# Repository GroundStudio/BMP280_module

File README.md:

GroundStudio BMP280 module
====================================

Get it from [ardushop.ro](https://ardushop.ro/ro/118-groundstudio)

Explore all the GroundStudio products at [GroundStudio.ro](https://groundstudio.ro/)

Description
-------------------
The module integrates the BMP280 temperature and atmospheric pressure sensor that uses the I²C and SPI standards for communication so it can be easily used together with most existing development boards.

Contents
-------------------

* [/Hardware](https://github.com/GroundStudio/BMP280_module/tree/main/Hardware) -- Schematics, layout.

Versions
-------------------
*(Not all tags shown)*

- [REV 1.0.0]

License
-------------------

This is released under the [Attribution-ShareAlike 4.0 International (CC BY-SA 4.0)](https://creativecommons.org/licenses/by-sa/4.0/) license.
**You are welcome to use this for commercial purposes.**

Please consider contributing back to this project or others to help the open-source hardware community continue to thrive and grow!

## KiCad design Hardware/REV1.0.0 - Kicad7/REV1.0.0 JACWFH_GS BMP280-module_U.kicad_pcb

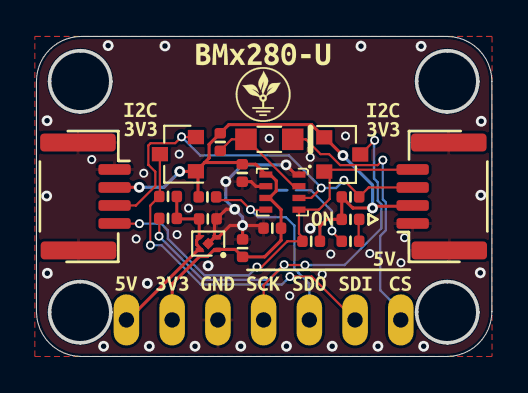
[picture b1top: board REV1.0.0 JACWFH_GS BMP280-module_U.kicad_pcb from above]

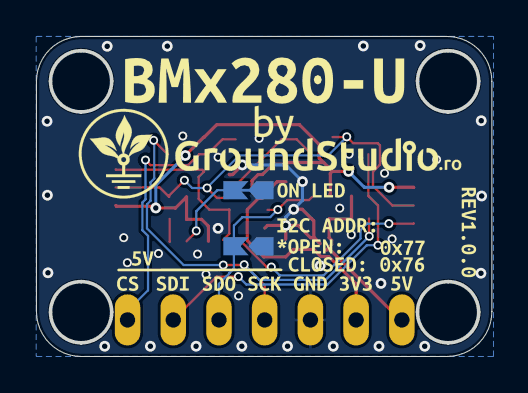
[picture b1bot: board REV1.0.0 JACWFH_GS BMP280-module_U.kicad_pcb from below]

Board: 2 copper layers, 25.2 x 17.6 mm, 51 parts (18 on the bottom side), 12 nets.

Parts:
C1, C2: C_0402_100nF_16V; C_0402_alt
C3, C4: C_0402_1uF_10V; C_0402_alt
D2: 1N4148WS; SOD-323
J1: Conn_01x07; PinHeader_1x07_P2.54mm_Vertical_Male
J2: LED disable; SolderJumper_NC
J4: SolderJumper_NO
LED1: ON_LED; LED_0402_alt
Q1, Q2: BSS138; SOT-23
R1, R2, R3, R4, R5, R6, R7: R_0402_10k; R_0402_alt
REG1: FBP1-1-4_ME6211C33U4AG-N; FBP1-1-4
U1: BMP280; LGA-8_2x2.5mm_BMP&BME280
X1, X2: SH_1x04_P1.0_H; SH__1x04_P1.00mm_Horizontal
kibuzzard-6343EE4B: G***; kibuzzard-6343EE4B
kibuzzard-6343F6DB: G***; kibuzzard-6343F6DB
kibuzzard-6343F70F: G***; kibuzzard-6343F70F
kibuzzard-6343F74A, kibuzzard-6343F74A#2: G***; kibuzzard-6343F74A
kibuzzard-6343F740, kibuzzard-6343F740#2: G***; kibuzzard-6343F740
kibuzzard-6343FCC8, kibuzzard-6343FCC8#2: G***; kibuzzard-6343FCC8
kibuzzard-6343FCE2: G***; kibuzzard-6343FCE2
kibuzzard-6343FCED, kibuzzard-6343FCED#2, kibuzzard-6343FCED#3, kibuzzard-6343FCED#4: G***; kibuzzard-6343FCED
kibuzzard-6343FD2F, kibuzzard-6343FD2F#2: G***; kibuzzard-6343FD2F
kibuzzard-6343FD19, kibuzzard-6343FD19#2: G***; kibuzzard-6343FD19
kibuzzard-6343FD42, kibuzzard-6343FD42#2: G***; kibuzzard-6343FD42
kibuzzard-6343FED9, kibuzzard-6343FED9#2: G***; kibuzzard-6343FED9
kibuzzard-6343FEE9, kibuzzard-6343FEE9#2: G***; kibuzzard-6343FEE9
kibuzzard-634406C2: G***; kibuzzard-634406C2
kibuzzard-634539A0: G***; kibuzzard-634539A0
kibuzzard-634539C0: G***; kibuzzard-634539C0
kibuzzard-634539DF: G***; kibuzzard-634539DF
kibuzzard-63440681: G***; kibuzzard-63440681

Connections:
+3V3: C1.1, C2.1, C4.1, J1.2, LED1.2 (A), Q1.1 (G), Q2.1 (G), R3.1, R5.1, R6.1, R7.1, REG1.1 (OUT), U1.6 (VDDIO), U1.8 (VDD), X1.2 (3V3), X2.2 (3V3)
+5V: C3.1, J1.1, R1.1, R2.1, REG1.3 (CE), REG1.4 (IN)
CS: D2.1 (K), J1.7
CSB_3V: D2.2 (A), R6.2, U1.2 (CSB)
GND: C1.2, C2.2, C3.2, C4.2, J1.3, J2.1, J4.1, REG1.2 (GND), REG1.5 (EXP), U1.1 (GND), U1.7 (GND), X1.0 (SHIELD), X1.1 (GND), X2.0 (SHIELD), X2.1 (GND)
unnamed: J2.2, R4.2
unnamed: LED1.1 (K), R4.1
SCK_3V: Q2.2 (S), R7.2, U1.4 (SCK), X1.4 (SCL), X2.4 (SCL)
SCK_SCL: J1.4, Q2.3 (D), R1.2
SDI_3V: Q1.2 (S), R3.2, U1.3 (SDI), X1.3 (SDA), X2.3 (SDA)
SDI_SDA: J1.6, Q1.3 (D), R2.2
SDO_ADR: J1.5, J4.2, R5.2, U1.5 (SDO)

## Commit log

2024-03-15 - initial commit
